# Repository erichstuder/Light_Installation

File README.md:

# Light_Installation

This is a research project do investigate MBSE (Model Based System Engineering) and a more classical textual approach. Both approaches are applied in parallel.

see online documentation: https://erichstuder.github.io/Light_Installation/

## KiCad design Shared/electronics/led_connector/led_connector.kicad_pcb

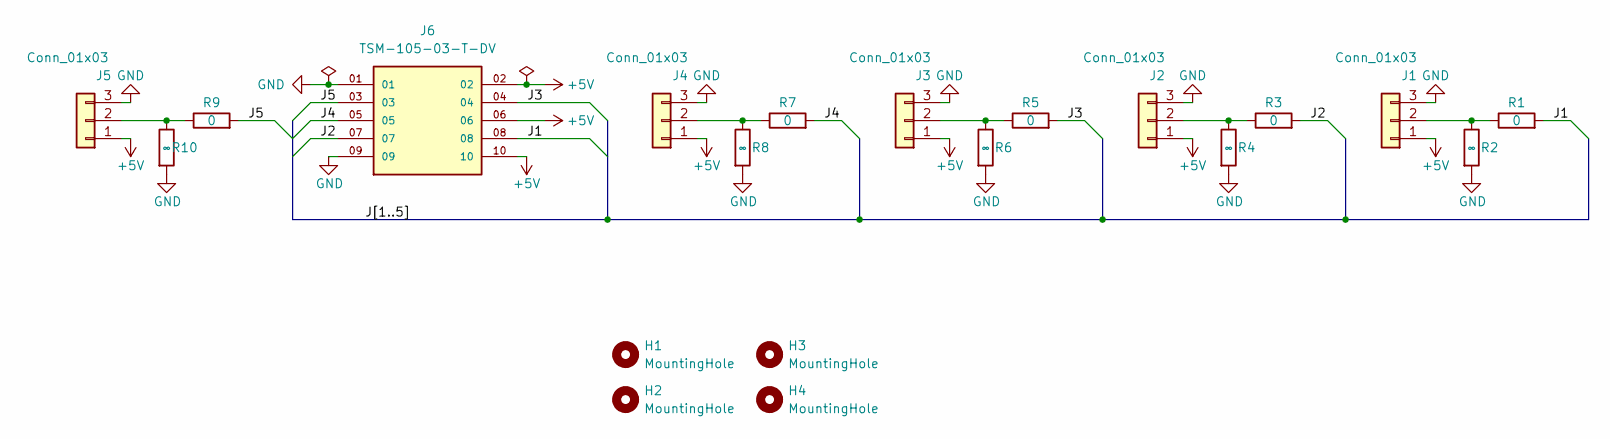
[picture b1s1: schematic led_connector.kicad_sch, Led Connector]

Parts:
H1, H2, H3, H4: MountingHole; MountingHole_3.2mm_M3
J1, J2, J3, J4, J5: Conn_01x03; 691508110303
J6: TSM-105-03-T-DV; SAMTEC_TSM-105-03-T-DV
R1, R3, R5, R7, R9: 0; R_0805_2012Metric
R2, R4, R6, R8, R10: ∞; R_0805_2012Metric

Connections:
+5V: J1.1, J2.1, J3.1, J4.1, J5.1, J6.02, J6.06, J6.10
/J1: J6.08, R1.2
/J2: J6.07, R3.2
/J3: J6.04, R5.2
/J4: J6.05, R7.2
/J5: J6.03, R9.2
GND: J1.3, J2.3, J3.3, J4.3, J5.3, J6.01, J6.09, R2.2, R4.2, R6.2, R8.2, R10.2
unnamed: J1.2, R1.1, R2.1
unnamed: J2.2, R3.1, R4.1
unnamed: J3.2, R5.1, R6.1
unnamed: J4.2, R7.1, R8.1
unnamed: J5.2, R9.1, R10.1

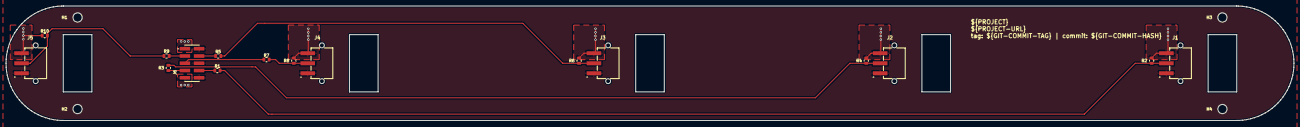
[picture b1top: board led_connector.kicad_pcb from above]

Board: 2 copper layers, 450.0 x 40.0 mm, 20 parts (0 on the bottom side), 12 nets.

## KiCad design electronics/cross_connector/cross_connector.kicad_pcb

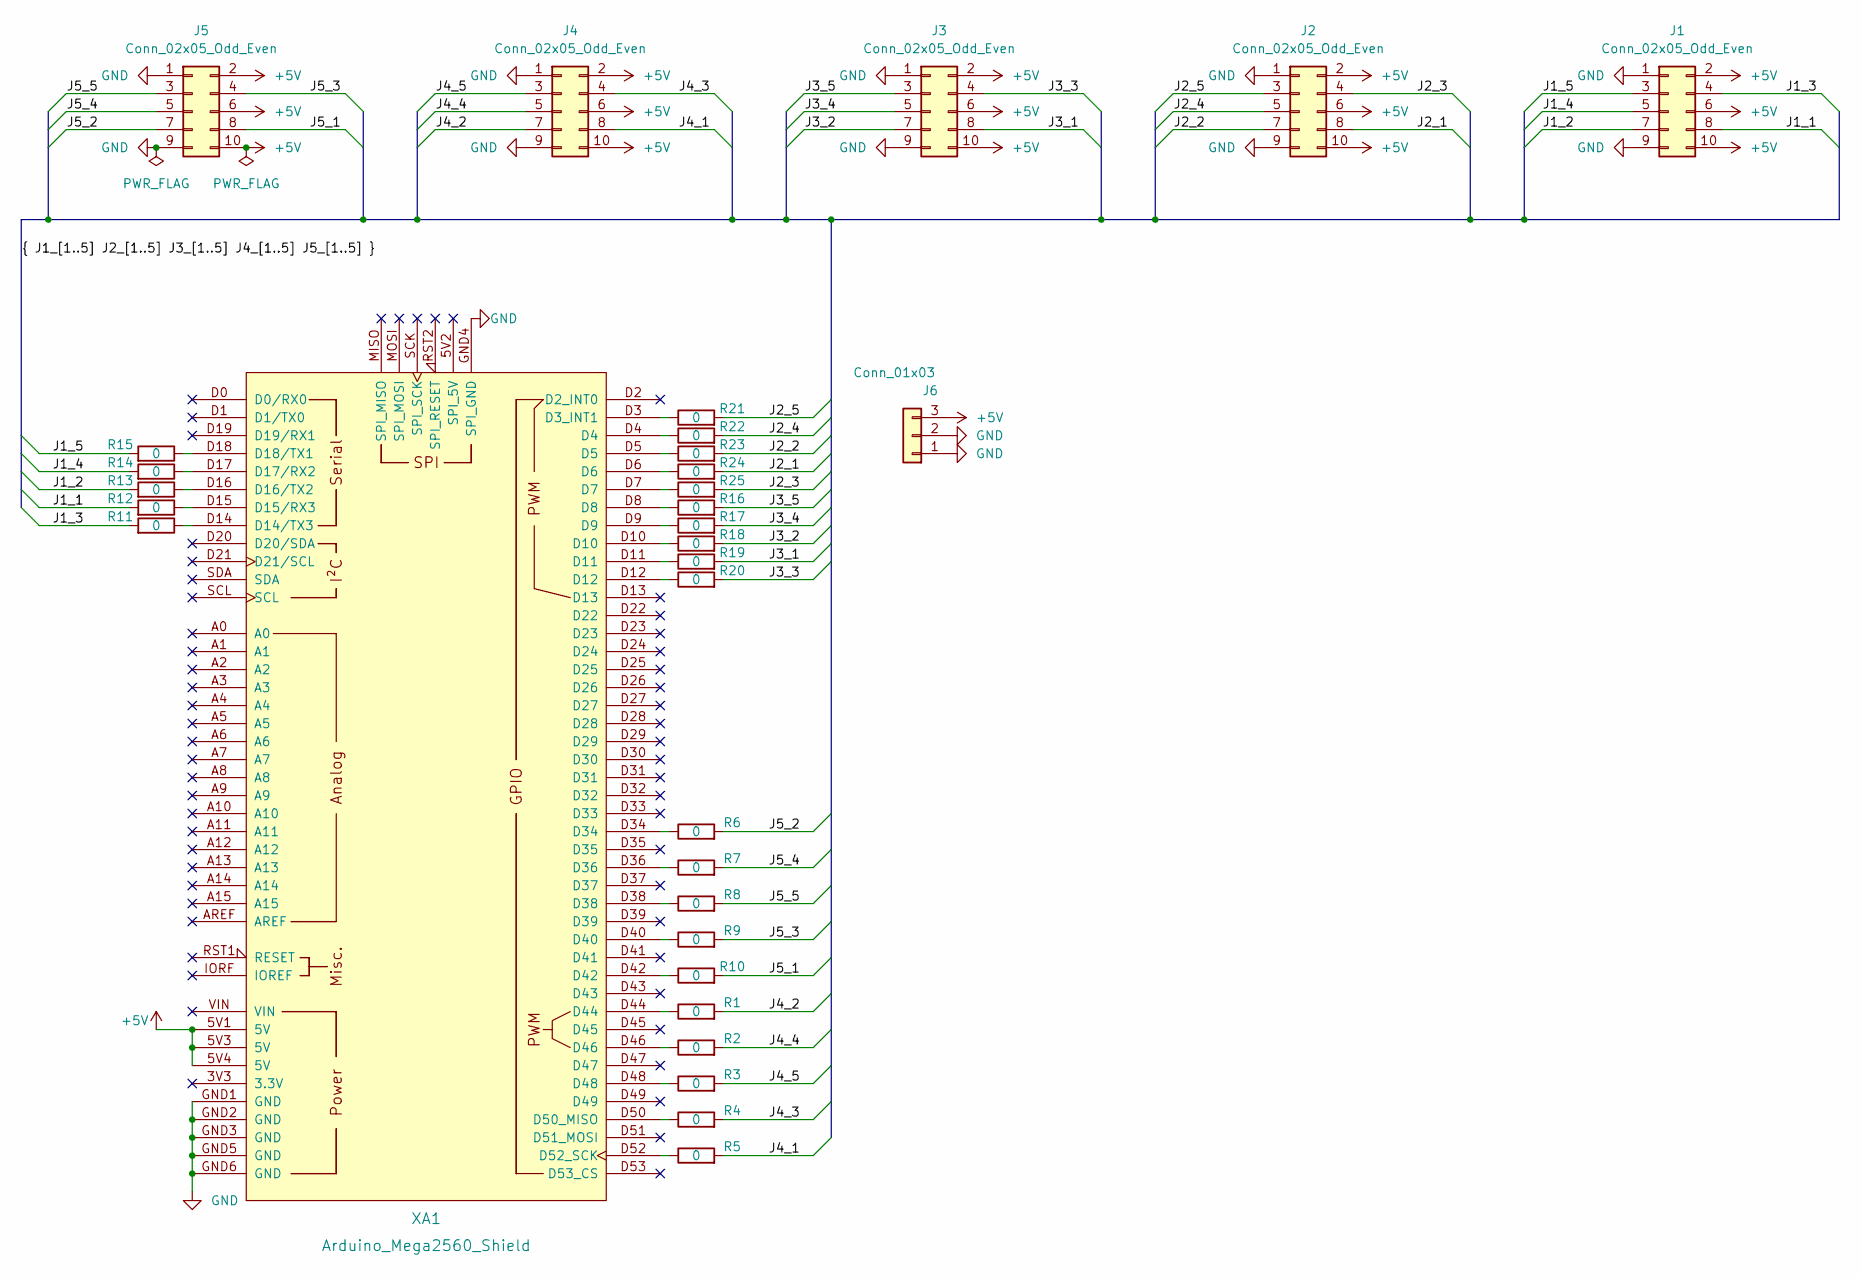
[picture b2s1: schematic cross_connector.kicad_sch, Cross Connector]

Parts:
J1, J2, J3, J4, J5: Conn_02x05_Odd_Even; PinSocket_2x05_P2.54mm_Vertical
J6: Conn_01x03; 691508110303
R1, R2, R3, R4, R5, R6, R7, R8, R9, R10, R11, R12, R13, R14, R15, R16, R17, R18, R19, R20, R21, R22, R23, R24, R25: 0; R_0805_2012Metric
XA1: Arduino_Mega2560_Shield

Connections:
+5V: J1.2, J1.6, J1.10, J2.2, J2.6, J2.10, J3.2, J3.6, J3.10, J4.2, J4.6, J4.10, J5.2, J5.6, J5.10, J6.3, XA1.5V1 (5V), XA1.5V3 (5V), XA1.5V4 (5V)
/J1_1: J1.8, R12.2
/J1_2: J1.7, R13.2
/J1_3: J1.4, R11.2
/J1_4: J1.5, R14.2
/J1_5: J1.3, R15.2
/J2_1: J2.8, R24.2
/J2_2: J2.7, R23.2
/J2_3: J2.4, R25.2
/J2_4: J2.5, R22.2
/J2_5: J2.3, R21.2
/J3_1: J3.8, R19.2
/J3_2: J3.7, R18.2
/J3_3: J3.4, R20.2
/J3_4: J3.5, R17.2
/J3_5: J3.3, R16.2
/J4_1: J4.8, R5.2
/J4_2: J4.7, R1.2
/J4_3: J4.4, R4.2
/J4_4: J4.5, R2.2
/J4_5: J4.3, R3.2
/J5_1: J5.8, R10.2
/J5_2: J5.7, R6.2
/J5_3: J5.4, R9.2
/J5_4: J5.5, R7.2
/J5_5: J5.3, R8.2
GND: J1.1, J1.9, J2.1, J2.9, J3.1, J3.9, J4.1, J4.9, J5.1, J5.9, J6.1, J6.2, XA1.GND1 (GND), XA1.GND2 (GND), XA1.GND3 (GND), XA1.GND4 (SPI_GND), XA1.GND5 (GND), XA1.GND6 (GND)
unnamed: R1.1, XA1.D44
unnamed: R2.1, XA1.D46
unnamed: R3.1, XA1.D48
unnamed: R4.1, XA1.D50 (D50_MISO)
unnamed: R5.1, XA1.D52 (D52_SCK)
unnamed: R6.1, XA1.D34
unnamed: R7.1, XA1.D36
unnamed: R8.1, XA1.D38
unnamed: R9.1, XA1.D40
unnamed: R10.1, XA1.D42
unnamed: R11.1, XA1.D14 (D14/TX3)
unnamed: R12.1, XA1.D15 (D15/RX3)
unnamed: R13.1, XA1.D16 (D16/TX2)
unnamed: R14.1, XA1.D17 (D17/RX2)
unnamed: R15.1, XA1.D18 (D18/TX1)
unnamed: R16.1, XA1.D8
unnamed: R17.1, XA1.D9
unnamed: R18.1, XA1.D10
unnamed: R19.1, XA1.D11
unnamed: R20.1, XA1.D12
unnamed: R21.1, XA1.D3 (D3_INT1)
unnamed: R22.1, XA1.D4
unnamed: R23.1, XA1.D5
unnamed: R24.1, XA1.D6
unnamed: R25.1, XA1.D7

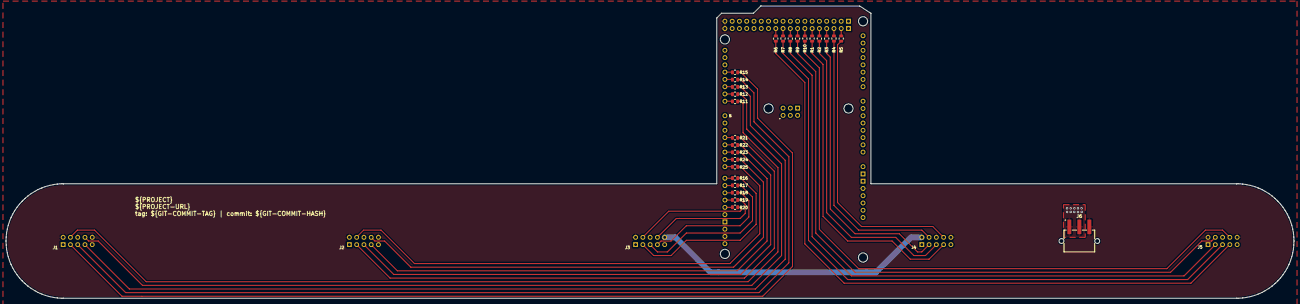
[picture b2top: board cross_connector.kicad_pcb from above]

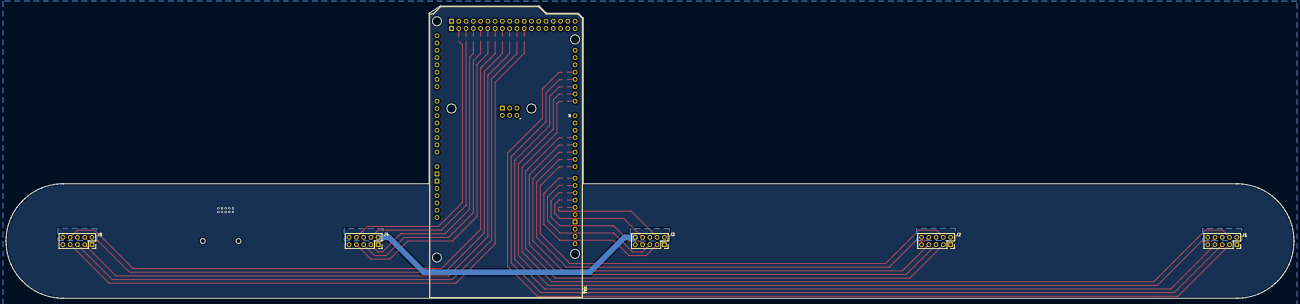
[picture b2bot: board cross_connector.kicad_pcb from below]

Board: 2 copper layers, 450.0 x 102.1 mm, 32 parts (5 on the bottom side), 52 nets.

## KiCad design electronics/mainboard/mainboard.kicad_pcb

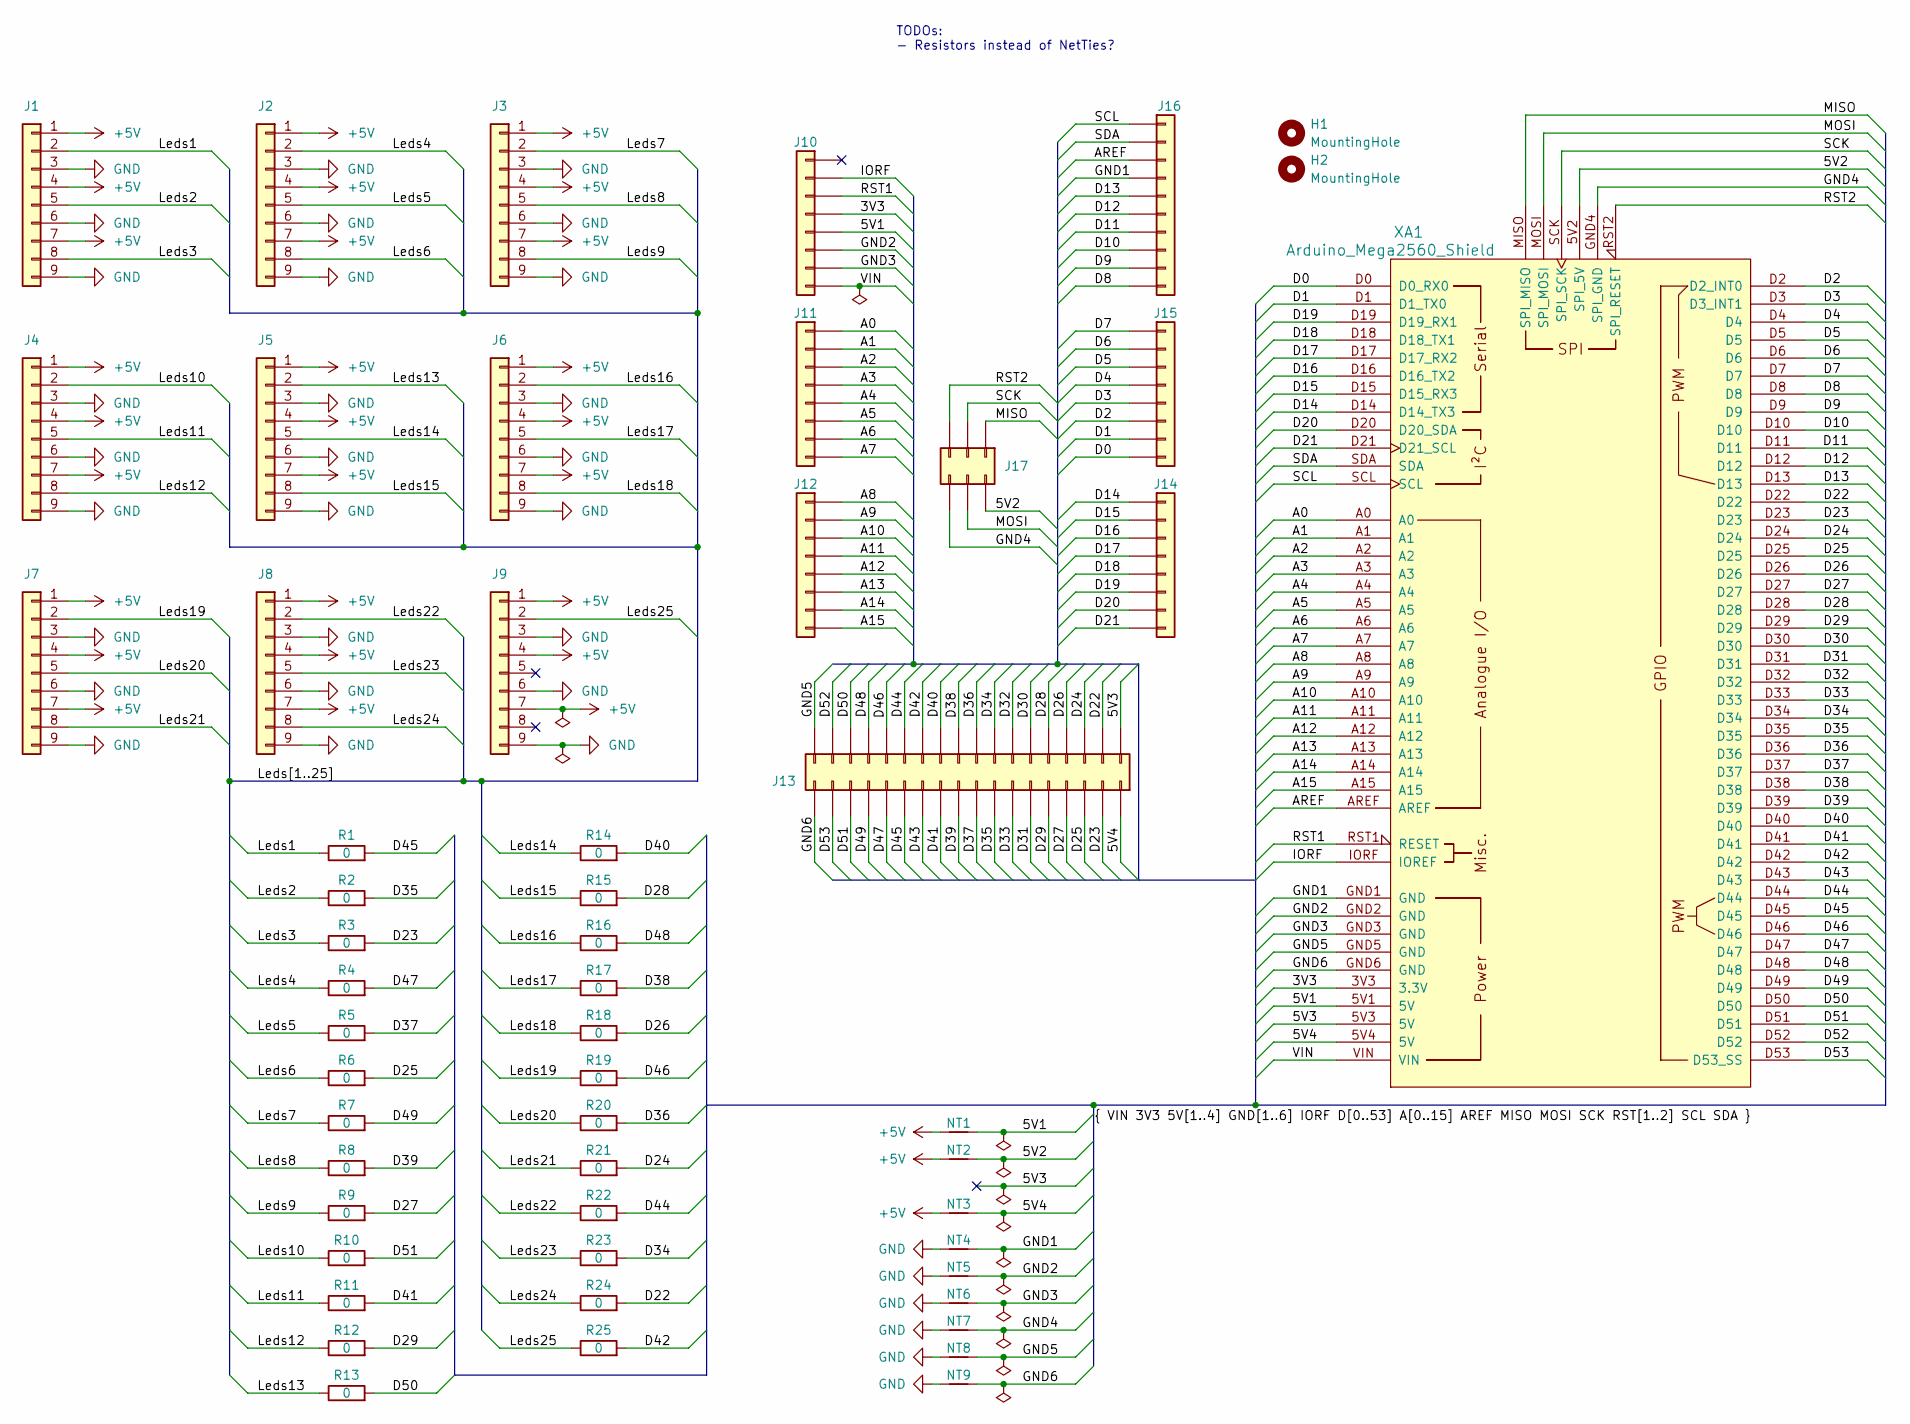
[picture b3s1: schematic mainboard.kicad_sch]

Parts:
H1, H2: MountingHole; MountingHole_3.2mm_M3
J1, J2, J3, J4, J5, J6, J7, J8, J9: Conn_01x09; 691247510009
J10, J11, J12, J14, J15: Conn_01x08; PinHeader_1x08_P2.54mm_Vertical_SMD_Pin1Right
J13: Conn_02x18_Odd_Even; PinHeader_2x18_P2.54mm_Vertical_SMD
J16: Conn_01x10; PinHeader_1x10_P2.54mm_Vertical_SMD_Pin1Right
J17: Conn_02x03_Odd_Even; PinSocket_2x03_P2.54mm_Vertical_SMD
NT1, NT2, NT3, NT4, NT5, NT6, NT7, NT8, NT9: NetTie_2; NetTie-2_SMD_Pad2.0mm
R1, R2, R3, R4, R5, R6, R7, R8, R9, R10, R11, R12, R13, R14, R15, R16, R17, R18, R19, R20, R21, R22, R23, R24, R25: 0; R_0805_2012Metric
XA1: Arduino_Mega2560_Shield

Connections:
+5V: J1.1, J1.4, J1.7, J2.1, J2.4, J2.7, J3.1, J3.4, J3.7, J4.1, J4.4, J4.7, J5.1, J5.4, J5.7, J6.1, J6.4, J6.7, J7.1, J7.4, J7.7, J8.1, J8.4, J8.7, J9.1, J9.4, J9.7, NT1.1, NT2.1, NT3.1
/3V3: J10.4, XA1.3V3 (3.3V)
/5V1: J10.5, NT1.2, XA1.5V1 (5V)
/5V2: J17.2, NT2.2, XA1.5V2 (SPI_5V)
/5V3: J13.2, XA1.5V3 (5V)
/5V4: J13.1, NT3.2, XA1.5V4 (5V)
/A0: J11.1, XA1.A0
/A1: J11.2, XA1.A1
/A2: J11.3, XA1.A2
/A3: J11.4, XA1.A3
/A4: J11.5, XA1.A4
/A5: J11.6, XA1.A5
/A6: J11.7, XA1.A6
/A7: J11.8, XA1.A7
/A8: J12.1, XA1.A8
/A9: J12.2, XA1.A9
/A10: J12.3, XA1.A10
/A11: J12.4, XA1.A11
/A12: J12.5, XA1.A12
/A13: J12.6, XA1.A13
/A14: J12.7, XA1.A14
/A15: J12.8, XA1.A15
/AREF: J16.3, XA1.AREF
/D0: J15.8, XA1.D0 (D0_RX0)
/D1: J15.7, XA1.D1 (D1_TX0)
/D2: J15.6, XA1.D2 (D2_INT0)
/D3: J15.5, XA1.D3 (D3_INT1)
/D4: J15.4, XA1.D4
/D5: J15.3, XA1.D5
/D6: J15.2, XA1.D6
/D7: J15.1, XA1.D7
/D8: J16.10, XA1.D8
/D9: J16.9, XA1.D9
/D10: J16.8, XA1.D10
/D11: J16.7, XA1.D11
/D12: J16.6, XA1.D12
/D13: J16.5, XA1.D13
/D14: J14.1, XA1.D14 (D14_TX3)
/D15: J14.2, XA1.D15 (D15_RX3)
/D16: J14.3, XA1.D16 (D16_TX2)
/D17: J14.4, XA1.D17 (D17_RX2)
/D18: J14.5, XA1.D18 (D18_TX1)
/D19: J14.6, XA1.D19 (D19_RX1)
/D20: J14.7, XA1.D20 (D20_SDA)
/D21: J14.8, XA1.D21 (D21_SCL)
/D22: J13.4, R24.2, XA1.D22
/D23: J13.3, R3.2, XA1.D23
/D24: J13.6, R21.2, XA1.D24
/D25: J13.5, R6.2, XA1.D25
/D26: J13.8, R18.2, XA1.D26
/D27: J13.7, R9.2, XA1.D27
/D28: J13.10, R15.2, XA1.D28
/D29: J13.9, R12.2, XA1.D29
/D30: J13.12, XA1.D30
/D31: J13.11, XA1.D31
/D32: J13.14, XA1.D32
/D33: J13.13, XA1.D33
/D34: J13.16, R23.2, XA1.D34
/D35: J13.15, R2.2, XA1.D35
/D36: J13.18, R20.2, XA1.D36
/D37: J13.17, R5.2, XA1.D37
/D38: J13.20, R17.2, XA1.D38
/D39: J13.19, R8.2, XA1.D39
/D40: J13.22, R14.2, XA1.D40
/D41: J13.21, R11.2, XA1.D41
/D42: J13.24, R25.2, XA1.D42
/D43: J13.23, XA1.D43
/D44: J13.26, R22.2, XA1.D44
/D45: J13.25, R1.2, XA1.D45
/D46: J13.28, R19.2, XA1.D46
/D47: J13.27, R4.2, XA1.D47
/D48: J13.30, R16.2, XA1.D48
/D49: J13.29, R7.2, XA1.D49
/D50: J13.32, R13.2, XA1.D50
/D51: J13.31, R10.2, XA1.D51
/D52: J13.34, XA1.D52
/D53: J13.33, XA1.D53 (D53_SS)
/GND1: J16.4, NT4.2, XA1.GND1 (GND)
/GND2: J10.6, NT5.2, XA1.GND2 (GND)
/GND3: J10.7, NT6.2, XA1.GND3 (GND)
/GND4: J17.6, NT7.2, XA1.GND4 (SPI_GND)
/GND5: J13.36, NT8.2, XA1.GND5 (GND)
/GND6: J13.35, NT9.2, XA1.GND6 (GND)
/IORF: J10.2, XA1.IORF (IOREF)
/Leds1: J1.2, R1.1
/Leds2: J1.5, R2.1
/Leds3: J1.8, R3.1
/Leds4: J2.2, R4.1
/Leds5: J2.5, R5.1
/Leds6: J2.8, R6.1
/Leds7: J3.2, R7.1
/Leds8: J3.5, R8.1
/Leds9: J3.8, R9.1
/Leds10: J4.2, R10.1
/Leds11: J4.5, R11.1
/Leds12: J4.8, R12.1
/Leds13: J5.2, R13.1
/Leds14: J5.5, R14.1
/Leds15: J5.8, R15.1
/Leds16: J6.2, R16.1
/Leds17: J6.5, R17.1
/Leds18: J6.8, R18.1
/Leds19: J7.2, R19.1
/Leds20: J7.5, R20.1
/Leds21: J7.8, R21.1
/Leds22: J8.2, R22.1
/Leds23: J8.5, R23.1
/Leds24: J8.8, R24.1
/Leds25: J9.2, R25.1
/MISO: J17.1, XA1.MISO (SPI_MISO)
/MOSI: J17.4, XA1.MOSI (SPI_MOSI)
/RST1: J10.3, XA1.RST1 (RESET)
/RST2: J17.5, XA1.RST2 (SPI_RESET)
/SCK: J17.3, XA1.SCK (SPI_SCK)
/SCL: J16.1, XA1.SCL
/SDA: J16.2, XA1.SDA
/VIN: J10.8, XA1.VIN
GND: J1.3, J1.6, J1.9, J2.3, J2.6, J2.9, J3.3, J3.6, J3.9, J4.3, J4.6, J4.9, J5.3, J5.6, J5.9, J6.3, J6.6, J6.9, J7.3, J7.6, J7.9, J8.3, J8.6, J8.9, J9.3, J9.6, J9.9, NT4.1, NT5.1, NT6.1, NT7.1, NT8.1, NT9.1

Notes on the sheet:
TODOs: - Resistors instead of NetTies?

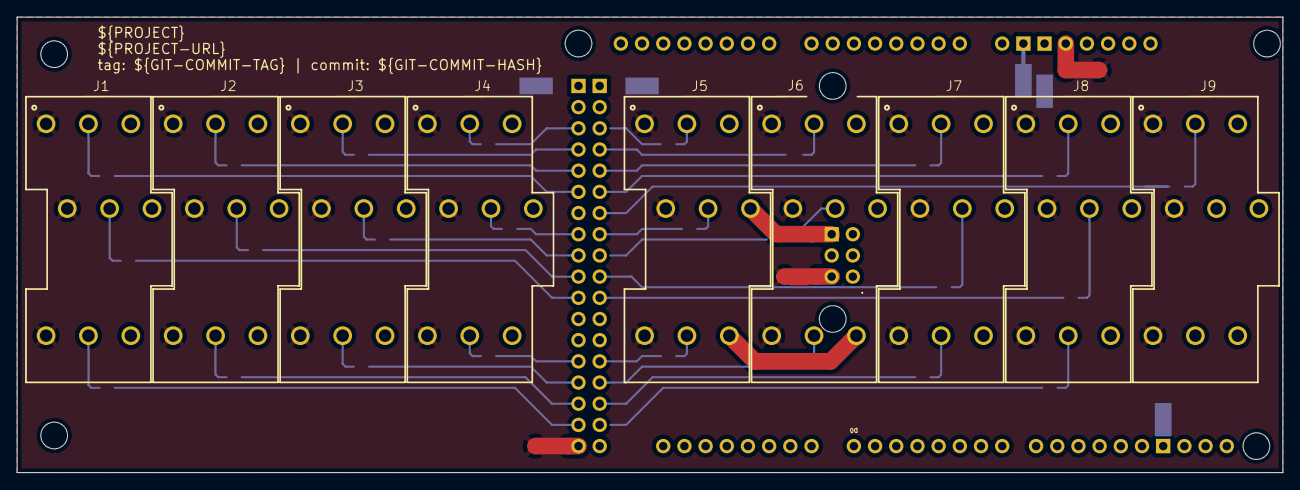
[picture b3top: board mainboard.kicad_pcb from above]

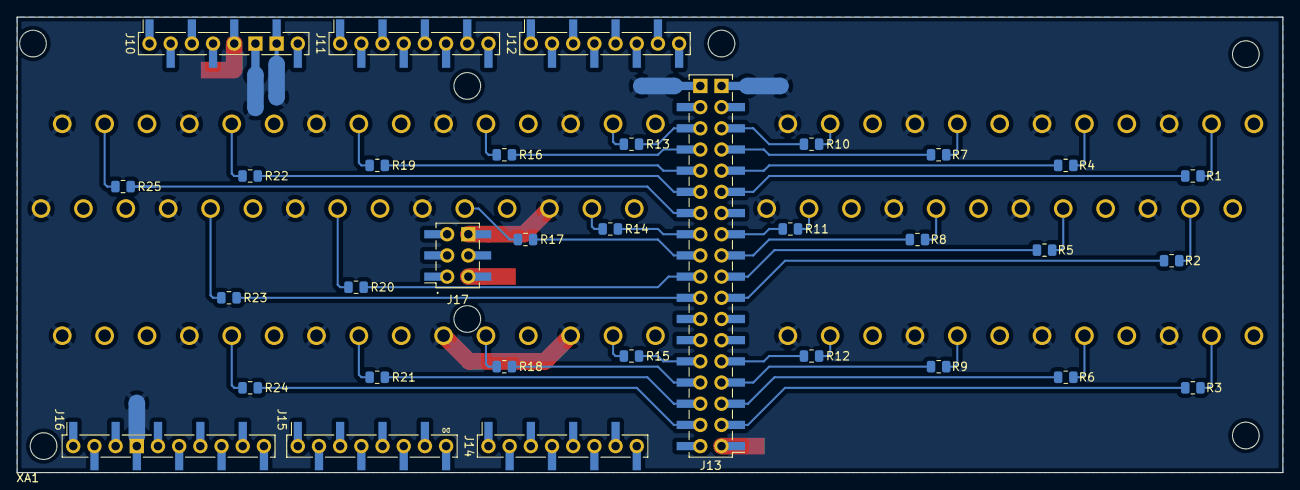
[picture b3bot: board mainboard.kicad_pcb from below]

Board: 2 copper layers, 151.8 x 54.6 mm, 54 parts (38 on the bottom side), 118 nets.

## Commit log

2022-09-19 simple led example
2022-09-19 2 strips on different pins
2022-10-15 plate drawn
2022-10-15 setup machnics release process
2022-10-19 add mounting holes
2022-11-20 clamp: improve and setup build queue
2022-12-17 rework for led-strip-channel
2022-12-17 remove reference to distance.scad
2022-12-18 create mainboard project
2022-12-19 add terminals
2022-12-19 place parts
2022-12-20 add and wire parts in schematic
2022-12-20 place parts on pcb
2022-12-20 route pcb
2022-12-20 drc check pass
2022-12-22 update FW for more strips
2022-12-22 reduce number of segments to handle all strips
2022-12-29 make the connectors a tht component
2022-12-29 add electronics workflows
2022-12-29 add project and version information
2022-12-29 solve erc and drc problems
2022-12-29 exclude some parts from bom
2022-12-31 modify for longer revision ID
2022-12-31 modify workflow to prevent warnings
2022-12-31 create electronics and modify firmware accordingly
2023-02-19 create rhapsody project
2023-02-19 ignore rpwx file
2023-02-19 add use case diagram
2023-02-19 modify use case diagram
2023-02-19 update some schematic symbols from library
2023-02-19 add type for Leds
2023-05-07 add led connector pcbs and remove mainboard
2023-05-13 rhapsody project created
2023-05-13 set view to flat
2023-05-13 add batch-file for convenient start-up
2023-05-13 move ignored content to correct place
2023-05-13 create component
2023-05-13 first time code generation for blinking example
2023-05-13 add an overview diagram
2023-05-13 reduce amount of use-cases
2023-05-20 control first led strip
2023-05-20 let all led strips blink
2023-05-23 change strip id to enum
2023-05-23 add test architecture and some mocks
2023-05-24 more work on code
2023-05-24 first running test
2023-05-25 correct the implementation to calculate the number of strips
2023-05-25 update before installing openscad
2023-05-28 everything compiles
2023-05-28 add more tests
2023-08-01 all leds white
2023-08-01 add led_simulation feature
2023-08-05 add steps template
2023-08-05 apt-get update before installation
2023-08-05 start the simulator
2023-08-05 first dot
2023-08-07 random blinking leds
2023-08-08 fading the red color
2023-08-10 print time per iteration
2023-08-14 led simulation with octave
2023-08-19 remove python files
2023-08-19 plot some leds
2023-08-19 add some color rule
2023-08-19 animation and more leds
2023-08-19 make animation endless
2023-08-19 create led coordinates
2023-08-19 bugfix
2023-08-19 running light
2023-09-04 build with cmake
2023-09-04 add build helper file for now
2023-09-04 add gnuplot example
2023-09-04 port running light into cpp
2023-09-04 create and animate pattern from C code
2023-09-04 running light on the device
2023-09-10 setup IntelliSense
2023-09-10 add wave pattern, refactoring and cleanup
2023-09-10 integrate patterns on microcontroller
2023-09-12 build cpputest docker image
2023-09-12 add example test
2023-09-12 add example test for actual code
2023-09-12 ignore coverage artefacts
2023-09-12 add properties file for IntelliSense
2023-09-12 move compilation artefacts to temp folder
2023-09-12 move unit tests to its own project-folder
2023-09-12 add mocks folder
2023-09-12 add tests for LedStrip
2023-09-12 automatically added files associations for cpp
2023-09-12 remove excessive newlines
2023-09-13 add tests for LedStrips
2023-09-13 add tests for LedStrip_Factory
2023-09-16 add shebang
2023-09-18 add docker file for cucumber-cpp
2023-09-24 add libboost-test-dev package to docker container
2023-09-24 cleanup Dockerfile
2023-09-30 prepare to run my step_definitions
2023-09-30 add dummy implementation of some steps
2023-10-07 add missing things
2023-10-07 add CMakeLists for cucumber
2023-10-07 hacky but it kinda works
2023-10-09 implement first test
2023-10-10 implement another test
2024-03-12 cleanup whitespaces
2024-03-14 cleanup
2024-08-11 add top level documentation for the split mbse<->textual
2024-08-11 move existing stuff to Shared folder
2024-08-11 add toolchain documentation to mbse
2024-08-17 add model project
2024-08-17 add generator project
2024-08-17 add setup documentation
2024-08-18 move images and add frame
2024-08-18 add documentation about the model
2024-08-20 update install documentation for acceleo
2024-08-20 modify indentation for better rendering
2024-08-20 upgrade acceleo and improve model and generator
2024-08-20 simple template to generate code from interfaces
2024-08-23 move interface generation to template
2024-08-23 remove irrelevant class
2024-08-23 generate class header and implementation from model
2024-08-23 use OpaqueBehavior with 'user code' areas
2024-08-23 add generation of constructors
2024-08-24 add external includes and ignore them for file generation
2024-08-24 optimize generation
2024-08-24 update data types
2024-08-24 optimize diagram
2024-08-24 add LedStrips block
2024-08-24 fix the model
2024-08-24 reorganize dependencies for better overview
2024-08-24 clarify links handling
2024-08-25 only add interfaces if the class has any
2024-08-25 add template to generate namespace header
2024-08-25 add a generated namespace header
2024-08-31 add template to generate a namespace file
2024-08-31 generator for namespace cpp file
2024-09-01 add use cases for simulator
2024-09-01 setup sphinx for use cases
2024-09-02 add use cases to textual implementation
2024-09-03 add device use cases
2024-09-03 add device use cases to model
2024-09-04 add and link some requirements
2024-09-04 add script to build electronics release locally - not yet working
2024-09-05 bugfixes in creation of production data
2024-09-05 correct file names
2024-09-05 optimize script
2024-09-05 remove unused comments
2024-09-07 add inspection items
2024-09-08 some cleanup
2024-09-08 link from main documentation to sub documentations
2024-09-10 requirements only for hw stuff
2024-09-10 move simulator and import features into documentation
2024-09-11 make simulator run
2024-09-11 remove gnuplot-iostream copy
2024-09-11 add gnuplot-iostream as a submodule
2024-09-11 update subrepo if necessary
2024-09-12 rework use-cases
2024-09-12 make cucumber tests compile
2024-09-12 move build artefacts into build folder
2024-09-12 add extension for gherkin
2024-09-12 add some coding rules
2024-09-12 make steps pass
2024-09-13 add linkage to features
2024-09-14 add python file for simulator cucumber tests
2024-09-14 cleanup script arguments
2024-09-14 integrate cucumber report into documentation
2024-09-14 implement build_all argument
2024-09-14 add documentation workflow
2024-09-14 disable pseudo tty for build_all
2024-09-14 update submodules before build all
2024-09-14 fetch all history
2024-09-16 add unit tests
2024-09-16 add coverage and report
2024-09-19 directly link from feature files
2024-09-19 simulator unit test infrastructure
2024-09-19 integrate unit_test coverage report
2024-09-21 optimize coverage report
2024-09-21 add some unit-tests
2024-09-21 add workflows for simulator feature-tests and unit-tests
2024-09-21 bug fixes in workflows
2024-09-21 get submodules
2024-09-21 add autogenerated files.associtations
2024-09-21 add more features
2024-09-21 update hash
2024-09-21 fix error in step text
2024-10-02 cleanup to run.py
2024-10-05 refactor top level run.py
2024-10-05 refactor top level run.py scripts
2024-10-05 refactor first executor file
2024-10-05 move get_caller_path to its own file
2024-10-05 refactor remaining executor scripts
2024-10-12 upgrade to sphinx needs 4.0.0
2024-10-12 add link to documentation to top level README.md
2024-10-16 add devcontainer for doc
2024-10-18 add dev container extenstion
2024-10-18 add devcontainer for Textual/doc
2024-10-18 remove unnecessary comments
2024-10-18 add devcontainer for Textual/simulator/features
2024-10-18 add devcontainer for Textual/simulator/unit_tests
2024-10-18 add devcontainer for MBSE/doc
2024-10-19 control containers via docker-compose
2024-10-19 install docker-compose
2024-10-19 handle TTY
2024-10-19 just a tryout
2024-10-19 prevent allocation of pseudo-TTY
2024-10-19 tty true should be overriden to false now
2024-10-19 bugfixes in workflows
2024-10-19 wait for docker-compose to finish taking down to prevent problems when starting the next container
2024-10-19 let subprocess check for errors
2024-10-19 cleanup Dockerfiles
2024-10-19 bugfix in path
2024-11-07 make file created by container editable by everyone
2024-11-08 remove old comments
2024-11-10 python scripts: add shebang and make executable
2024-11-16 simplify call of python scripts
2024-11-16 simplify execution of python scripts in build jobs
